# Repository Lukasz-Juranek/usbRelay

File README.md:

# USB
USB relay project, see [ucandevices](https://ucandevices.github.io) web page for full info.

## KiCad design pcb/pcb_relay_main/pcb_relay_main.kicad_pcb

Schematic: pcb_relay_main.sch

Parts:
C1: 0,47u; C_0603
C2: 1u; C_0603
C3: 100u; C_0603
J1: PROG; prog_con
J2: USB_A; USB_Mini-B
J3: Conn_01x10; Pin_Header_Straight_1x10_Pitch2.54mm
U1: PIC16(L)F1455-I_ST; SSOP-14

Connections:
+5V: C2.1, C3.1, J1.2, J2.1, J3.1, U1.1 (VDD)
GND: C1.2, C2.2, C3.2, J1.3, J2.4, J2.5, J3.10, U1.14 (VSS)
ICSPCLK: J1.5, J3.3, U1.9 (ICSPCLK/SDI/SDA/~CWGFLT~/C2IN-/C1IN-/AN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)
ICSPDAT: J1.4, J3.2, U1.10 (ICSPDAT/SCK/SCL/C2IN+/C1IN+/Vref+/AN4/R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)
unnamed: C1.1, U1.11 (Vusb3v3)
unnamed: J2.2, U1.12 (RA1/D-/ICSPCLK)
unnamed: J2.3, U1.13 (RA0/D+/ICSPDAT)
unnamed: J3.4, U1.8 (SDO/C2IN2-/C1IN2-/DACOUT1/AN6/RC2)
unnamed: J3.5, U1.7 (CLKR/~SS~/PWM2/C1IN3-/C2IN3-/DACOUT2/AN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)
unnamed: J3.6, U1.6 (CK/TK/CWG1B/C1OUT/C2OUT/RC4)
unnamed: J3.7, U1.5 (PWM1/DT/RX/CWG1A/T0CKI/RC5)
RA4: J3.8, U1.3 (RA4/AN3/SOSCO/T1G/SDO/CLKOUT/OSC2/CLKR)
RA5: J3.9, U1.2 (RA5/SOSCI/T1CKI/PWM2/CLKIN/OSC1)
VPP: J1.1, U1.4 (RA3/T1G/~SS~/~MCLR~/Vpp)

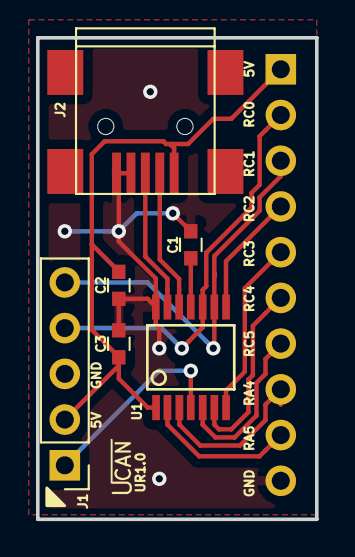
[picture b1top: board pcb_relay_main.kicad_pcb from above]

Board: 2 copper layers, 15.5 x 26.8 mm, 7 parts (1 on the bottom side), 14 nets.

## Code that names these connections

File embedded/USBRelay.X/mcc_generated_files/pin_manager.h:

/**
  @Generated Pin Manager Header File

  @Company:
    Microchip Technology Inc.

  @File Name:
    pin_manager.h

  @Summary:
    This is the Pin Manager file generated using PIC10 / PIC12 / PIC16 / PIC18 MCUs

  @Description
    This header file provides APIs for driver for .
    Generation Information :
        Product Revision  :  PIC10 / PIC12 / PIC16 / PIC18 MCUs - 1.65.2
        Device            :  PIC16F1455
        Driver Version    :  2.11
    The generated drivers are tested against the following:
        Compiler          :  XC8 1.45
        MPLAB 	          :  MPLAB X 4.15	
*/

/*
    (c) 2018 Microchip Technology Inc. and its subsidiaries. 
    
    Subject to your compliance with these terms, you may use Microchip software and any 
    derivatives exclusively with Microchip products. It is your responsibility to comply with third party 
    license terms applicable to your use of third party software (including open source software) that 
    may accompany Microchip software.
    
    THIS SOFTWARE IS SUPPLIED BY MICROCHIP "AS IS". NO WARRANTIES, WHETHER 
    EXPRESS, IMPLIED OR STATUTORY, APPLY TO THIS SOFTWARE, INCLUDING ANY 
    IMPLIED WARRANTIES OF NON-INFRINGEMENT, MERCHANTABILITY, AND FITNESS 
    FOR A PARTICULAR PURPOSE.
    
    IN NO EVENT WILL MICROCHIP BE LIABLE FOR ANY INDIRECT, SPECIAL, PUNITIVE, 
    INCIDENTAL OR CONSEQUENTIAL LOSS, DAMAGE, COST OR EXPENSE OF ANY KIND 
    WHATSOEVER RELATED TO THE SOFTWARE, HOWEVER CAUSED, EVEN IF MICROCHIP 
    HAS BEEN ADVISED OF THE POSSIBILITY OR THE DAMAGES ARE FORESEEABLE. TO 
    THE FULLEST EXTENT ALLOWED BY LAW, MICROCHIP'S TOTAL LIABILITY ON ALL 
    CLAIMS IN ANY WAY RELATED TO THIS SOFTWARE WILL NOT EXCEED THE AMOUNT 
    OF FEES, IF ANY, THAT YOU HAVE PAID DIRECTLY TO MICROCHIP FOR THIS 
    SOFTWARE.
*/

#ifndef PIN_MANAGER_H
#define PIN_MANAGER_H

#define INPUT   1
#define OUTPUT  0

#define HIGH    1
#define LOW     0

#define ANALOG      1
#define DIGITAL     0

#define PULL_UP_ENABLED      1
#define PULL_UP_DISABLED     0

// get/set RA0 procedures
#define RA0_GetValue()              PORTAbits.RA0

// get/set RA1 procedures
#define RA1_GetValue()              PORTAbits.RA1

// get/set R6 aliases
#define R6_TRIS                 TRISAbits.TRISA4
#define R6_LAT                  LATAbits.LATA4
#define R6_PORT                 PORTAbits.RA4
#define R6_WPU                  WPUAbits.WPUA4
#define R6_ANS                  ANSELAbits.ANSA4
#define R6_SetHigh()            do { LATAbits.LATA4 = 1; } while(0)
#define R6_SetLow()             do { LATAbits.LATA4 = 0; } while(0)
#define R6_Toggle()             do { LATAbits.LATA4 = ~LATAbits.LATA4; } while(0)
#define R6_GetValue()           PORTAbits.RA4
#define R6_SetDigitalInput()    do { TRISAbits.TRISA4 = 1; } while(0)
#define R6_SetDigitalOutput()   do { TRISAbits.TRISA4 = 0; } while(0)
#define R6_SetPullup()          do { WPUAbits.WPUA4 = 1; } while(0)
#define R6_ResetPullup()        do { WPUAbits.WPUA4 = 0; } while(0)
#define R6_SetAnalogMode()      do { ANSELAbits.ANSA4 = 1; } while(0)
#define R6_SetDigitalMode()     do { ANSELAbits.ANSA4 = 0; } while(0)

// get/set R7 aliases
#define R7_TRIS                 TRISAbits.TRISA5
#define R7_LAT                  LATAbits.LATA5
#define R7_PORT                 PORTAbits.RA5
#define R7_WPU                  WPUAbits.WPUA5
#define R7_SetHigh()            do { LATAbits.LATA5 = 1; } while(0)
#define R7_SetLow()             do { LATAbits.LATA5 = 0; } while(0)
#define R7_Toggle()             do { LATAbits.LATA5 = ~LATAbits.LATA5; } while(0)
#define R7_GetValue()           PORTAbits.RA5
#define R7_SetDigitalInput()    do { TRISAbits.TRISA5 = 1; } while(0)
#define R7_SetDigitalOutput()   do { TRISAbits.TRISA5 = 0; } while(0)
#define R7_SetPullup()          do { WPUAbits.WPUA5 = 1; } while(0)
#define R7_ResetPullup()        do { WPUAbits.WPUA5 = 0; } while(0)

// get/set R0 aliases
#define R0_TRIS                 TRISCbits.TRISC0
#define R0_LAT                  LATCbits.LATC0
#define R0_PORT                 PORTCbits.RC0
#define R0_ANS                  ANSELCbits.ANSC0
#define R0_SetHigh()            do { LATCbits.LATC0 = 1; } while(0)
#define R0_SetLow()             do { LATCbits.LATC0 = 0; } while(0)
#define R0_Toggle()             do { LATCbits.LATC0 = ~LATCbits.LATC0; } while(0)
#define R0_GetValue()           PORTCbits.RC0
#define R0_SetDigitalInput()    do { TRISCbits.TRISC0 = 1; } while(0)
#define R0_SetDigitalOutput()   do { TRISCbits.TRISC0 = 0; } while(0)
#define R0_SetAnalogMode()      do { ANSELCbits.ANSC0 = 1; } while(0)
#define R0_SetDigitalMode()     do { ANSELCbits.ANSC0 = 0; } while(0)

// get/set R1 aliases
#define R1_TRIS                 TRISCbits.TRISC1
#define R1_LAT                  LATCbits.LATC1
#define R1_PORT                 PORTCbits.RC1
#define R1_ANS                  ANSELCbits.ANSC1
#define R1_SetHigh()            do { LATCbits.LATC1 = 1; } while(0)
#define R1_SetLow()             do { LATCbits.LATC1 = 0; } while(0)
#define R1_Toggle()             do { LATCbits.LATC1 = ~LATCbits.LATC1; } while(0)
#define R1_GetValue()           PORTCbits.RC1
#define R1_SetDigitalInput()    do { TRISCbits.TRISC1 = 1; } while(0)
#define R1_SetDigitalOutput()   do { TRISCbits.TRISC1 = 0; } while(0)
#define R1_SetAnalogMode()      do { ANSELCbits.ANSC1 = 1; } while(0)
#define R1_SetDigitalMode()     do { ANSELCbits.ANSC1 = 0; } while(0)

// get/set R2 aliases
#define R2_TRIS                 TRISCbits.TRISC2
#define R2_LAT                  LATCbits.LATC2
#define R2_PORT                 PORTCbits.RC2
#define R2_ANS                  ANSELCbits.ANSC2
#define R2_SetHigh()            do { LATCbits.LATC2 = 1; } while(0)
#define R2_SetLow()             do { LATCbits.LATC2 = 0; } while(0)
#define R2_Toggle()             do { LATCbits.LATC2 = ~LATCbits.LATC2; } while(0)
#define R2_GetValue()           PORTCbits.RC2
#define R2_SetDigitalInput()    do { TRISCbits.TRISC2 = 1; } while(0)
#define R2_SetDigitalOutput()   do { TRISCbits.TRISC2 = 0; } while(0)
#define R2_SetAnalogMode()      do { ANSELCbits.ANSC2 = 1; } while(0)
#define R2_SetDigitalMode()     do { ANSELCbits.ANSC2 = 0; } while(0)

// get/set R3 aliases
#define R3_TRIS                 TRISCbits.TRISC3
#define R3_LAT                  LATCbits.LATC3
#define R3_PORT                 PORTCbits.RC3
#define R3_ANS                  ANSELCbits.ANSC3
#define R3_SetHigh()            do { LATCbits.LATC3 = 1; } while(0)
#define R3_SetLow()             do { LATCbits.LATC3 = 0; } while(0)
#define R3_Toggle()             do { LATCbits.LATC3 = ~LATCbits.LATC3; } while(0)
#define R3_GetValue()           PORTCbits.RC3
#define R3_SetDigitalInput()    do { TRISCbits.TRISC3 = 1; } while(0)
#define R3_SetDigitalOutput()   do { TRISCbits.TRISC3 = 0; } while(0)
#define R3_SetAnalogMode()      do { ANSELCbits.ANSC3 = 1; } while(0)
#define R3_SetDigitalMode()     do { ANSELCbits.ANSC3 = 0; } while(0)

// get/set R4 aliases
#define R4_TRIS                 TRISCbits.TRISC4
#define R4_LAT                  LATCbits.LATC4
#define R4_PORT                 PORTCbits.RC4
#define R4_SetHigh()            do { LATCbits.LATC4 = 1; } while(0)
#define R4_SetLow()             do { LATCbits.LATC4 = 0; } while(0)
#define R4_Toggle()             do { LATCbits.LATC4 = ~LATCbits.LATC4; } while(0)
#define R4_GetValue()           PORTCbits.RC4
#define R4_SetDigitalInput()    do { TRISCbits.TRISC4 = 1; } while(0)
#define R4_SetDigitalOutput()   do { TRISCbits.TRISC4 = 0; } while(0)

// get/set R5 aliases
#define R5_TRIS                 TRISCbits.TRISC5
#define R5_LAT                  LATCbits.LATC5
#define R5_PORT                 PORTCbits.RC5
#define R5_SetHigh()            do { LATCbits.LATC5 = 1; } while(0)
#define R5_SetLow()             do { LATCbits.LATC5 = 0; } while(0)
#define R5_Toggle()             do { LATCbits.LATC5 = ~LATCbits.LATC5; } while(0)
#define R5_GetValue()           PORTCbits.RC5
#define R5_SetDigitalInput()    do { TRISCbits.TRISC5 = 1; } while(0)
#define R5_SetDigitalOutput()   do { TRISCbits.TRISC5 = 0; } while(0)

/**
   @Param
    none
   @Returns
    none
   @Description
    GPIO and peripheral I/O initialization
   @Example
    PIN_MANAGER_Initialize();
 */
void PIN_MANAGER_Initialize (void);

/**
 * @Param
    none
 * @Returns
    none
 * @Description
    Interrupt on Change Handling routine
 * @Example
    PIN_MANAGER_IOC();
 */
void PIN_MANAGER_IOC(void);



#endif // PIN_MANAGER_H
/**
 End of File
*/

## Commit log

2018-09-18 Init
2018-09-21 Unit test addition
2018-09-29 Added steps
2018-10-01 add Test for parsing
2018-10-04 Working CDC USB
2018-10-06 Tests update
2018-10-08 Update app
2018-10-09 Add flash config
2018-10-16 USB fix
2018-10-17 Examples add and NVM fix
2018-10-18 NVM fix
2018-11-29 Add CLR command change isr period to 100 ms
2019-01-03 Timer update
